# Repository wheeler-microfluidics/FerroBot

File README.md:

# FerroBot

First attempt of making a FerroBot based on https://github.com/The-Brainery/FerroBot.

This version has the option to be controlled via microcontroller or the FerroBot controller board (https://github.com/wheeler-microfluidics/FerroBot-Button-Controller.kicad)

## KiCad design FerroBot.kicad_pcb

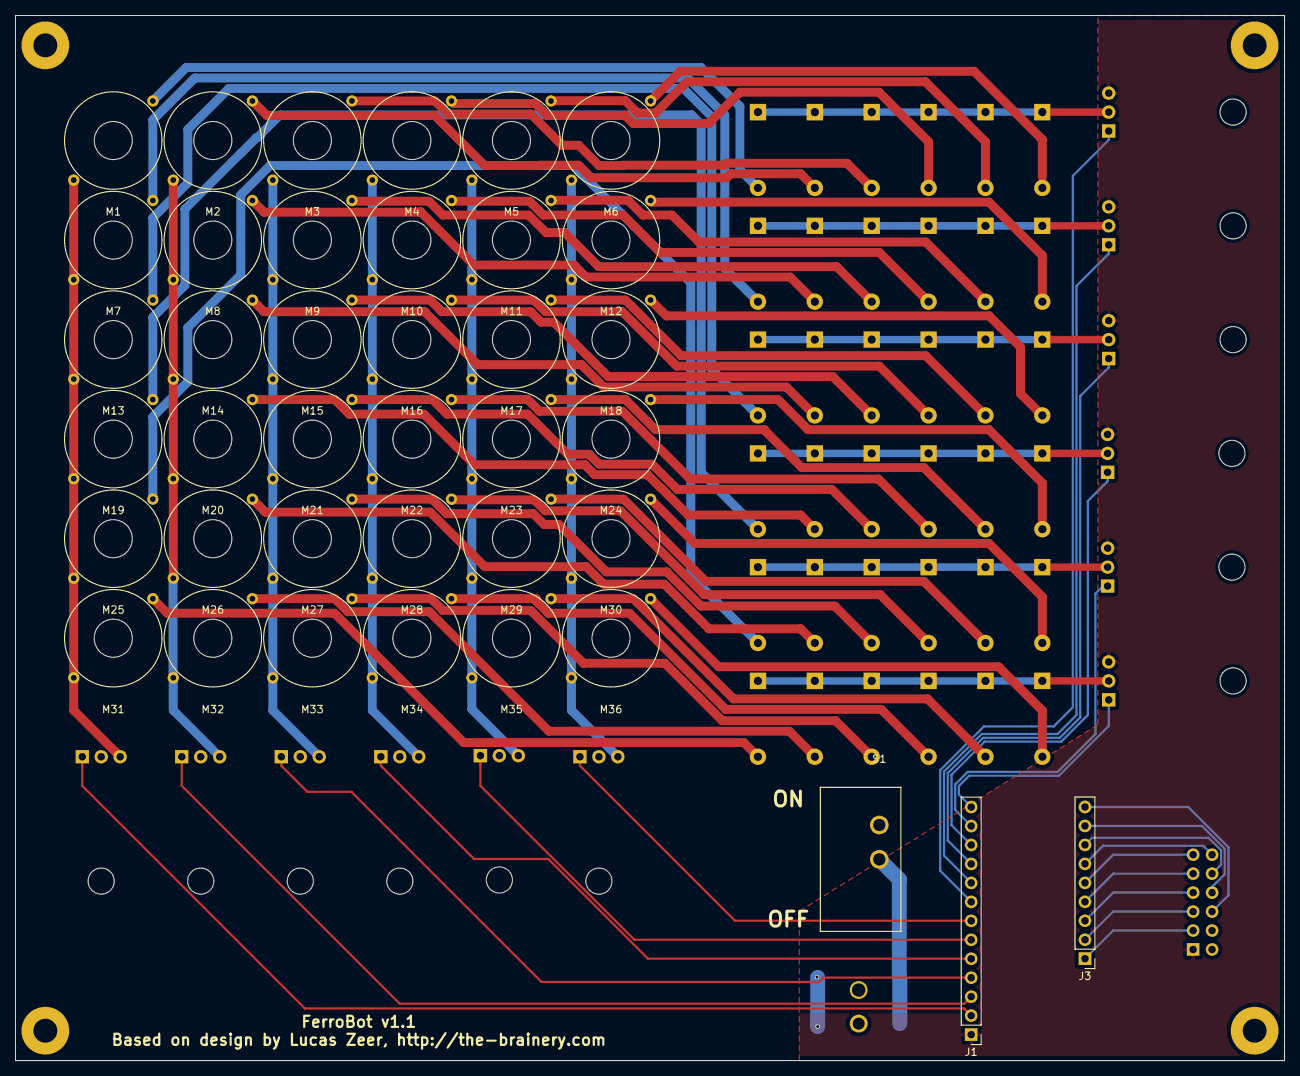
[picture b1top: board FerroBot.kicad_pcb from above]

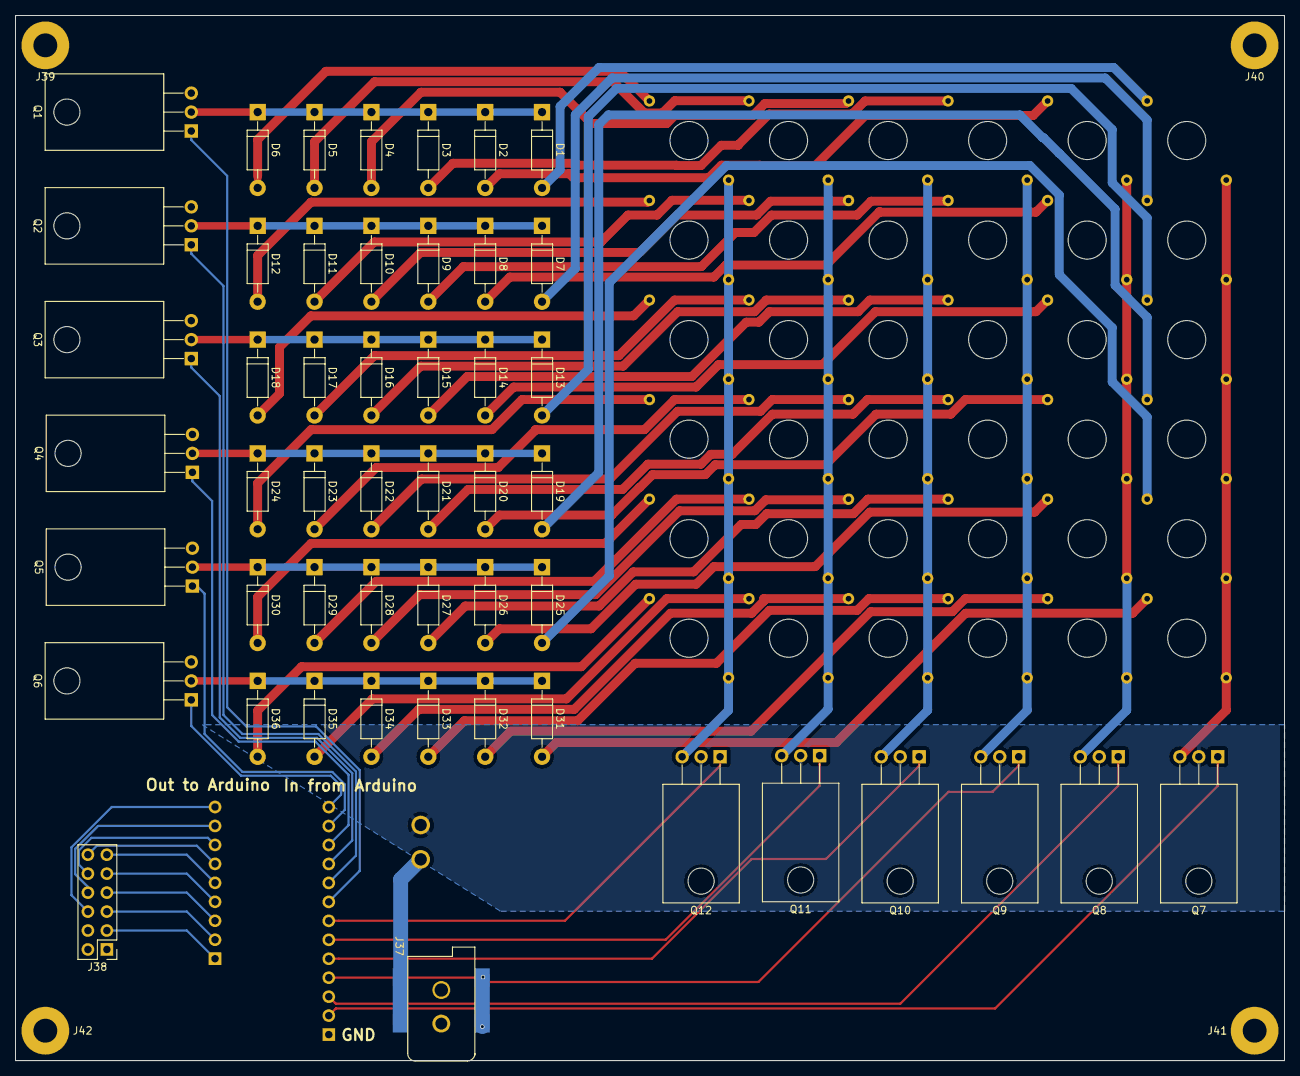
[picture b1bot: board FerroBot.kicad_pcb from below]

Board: 2 copper layers, 170.0 x 140.0 mm, 93 parts (54 on the bottom side), 72 nets.

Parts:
D1, D2, D3, D4, D5, D6, D7, D8, D9, D10, D11, D12, D13, D14, D15, D16, D17, D18, D19, D20, D21, D22, D23, D24, D25, D26, D27, D28, D29, D30, D31, D32, D33, D34, D35, D36: D_Schottky; D_DO-41_SOD81_P10.16mm_Horizontal
J1: Conn_01x13; Pin_Header_Straight_1x13_Pitch2.54mm
J3: Conn_01x09; Pin_Header_Straight_1x09_Pitch2.54mm
J37: BARREL_JACK; DC_JACK_SMD
J38: CONN_02X06; Pin_Header_Straight_2x06_Pitch2.54mm
J39, J40, J41, J42: CONN_01X01; MountingHole_3.2mm_M3_Pad
M1, M2, M3, M4, M5, M6, M7, M8, M9, M10, M11, M12, M13, M14, M15, M16, M17, M18, M19, M20, M21, M22, M23, M24, M25, M26, M27, M28, M29, M30, M31, M32, M33, M34, M35, M36: FERROBOT_MAGNET; Ferrobot_Magnet
Q1, Q2, Q3, Q4, Q5, Q6, Q7, Q8, Q9, Q10, Q11, Q12: Q_NMOS_DGS; TO-220-3_Horizontal
S1: SPST; L101_Switch

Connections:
C1CONTROL: J1.8, Q1.1
C2CONTROL: J1.9, Q2.1
C3CONTROL: J1.10, Q3.1
C4CONTROL: J1.11, Q4.1
C5CONTROL: J1.12, Q5.1
C6CONTROL: J1.13, Q6.1
COLUMN1: D1.1, D2.1, D3.1, D4.1, D5.1, D6.1, Q1.2
COLUMN2: D7.1, D8.1, D9.1, D10.1, D11.1, D12.1, Q2.2
COLUMN3: D13.1, D14.1, D15.1, D16.1, D17.1, D18.1, Q3.2
COLUMN4: D19.1, D20.1, D21.1, D22.1, D23.1, D24.1, Q4.2
COLUMN5: D25.1, D26.1, D27.1, D28.1, D29.1, D30.1, Q5.2
COLUMN6: D31.1, D32.1, D33.1, D34.1, D35.1, D36.1, Q6.2
DIODE1: D1.2, M1.2
DIODE2: D2.2, M2.2
DIODE3: D3.2, M3.2
DIODE4: D4.2, M4.2
DIODE5: D5.2, M5.2
DIODE6: D6.2, M6.2
DIODE7: D7.2, M7.2
DIODE8: D8.2, M8.2
DIODE9: D9.2, M9.2
DIODE10: D10.2, M10.2
DIODE11: D11.2, M11.2
DIODE12: D12.2, M12.2
DIODE13: D13.2, M13.2
DIODE14: D14.2, M14.2
DIODE15: D15.2, M15.2
DIODE16: D16.2, M16.2
DIODE17: D17.2, M17.2
DIODE18: D18.2, M18.2
DIODE19: D19.2, M19.2
DIODE20: D20.2, M20.2
DIODE21: D21.2, M21.2
DIODE22: D22.2, M22.2
DIODE23: D23.2, M23.2
DIODE24: D24.2, M24.2
DIODE25: D25.2, M25.2
DIODE26: D26.2, M26.2
DIODE27: D27.2, M27.2
DIODE28: D28.2, M28.2
DIODE29: D29.2, M29.2
DIODE30: D30.2, M30.2
DIODE31: D31.2, M31.2
DIODE32: D32.2, M32.2
DIODE33: D33.2, M33.2
DIODE34: D34.2, M34.2
DIODE35: D35.2, M35.2
DIODE36: D36.2, M36.2
GND: J1.1, J37.1, J37.2, J38.1, Q1.3, Q2.3, Q3.3, Q4.3, Q5.3, Q6.3
MAGNET1: J3.1, J38.3
MAGNET2: J3.2, J38.5
MAGNET3: J3.3, J38.7
MAGNET4: J3.4, J38.9
MAGNET5: J3.5, J38.11
MAGNET6: J3.6, J38.12
MAGNET7: J3.7, J38.10
MAGNET8: J3.8, J38.8
MAGNET9: J3.9, J38.6
PWR: Q7.2, Q9.2, Q10.2, Q11.2, Q12.2, S1.1
PWR_SWITCH: J37.3, S1.2
R1CONTROL: J1.2, Q7.1
R2CONTROL: J1.3, Q8.1
R3CONTROL: J1.4, Q9.1
R4CONTROL: J1.5, Q10.1
R5CONTROL: J1.6, Q11.1
R6CONTROL: J1.7, Q12.1
ROW1: M1.1, M7.1, M13.1, M19.1, M25.1, M31.1, Q7.3
ROW2: M2.1, M8.1, M14.1, M20.1, M26.1, M32.1, Q8.3
ROW3: M3.1, M9.1, M15.1, M21.1, M27.1, M33.1, Q9.3
ROW4: M4.1, M10.1, M16.1, M22.1, M28.1, M34.1, Q10.3
ROW5: M5.1, M11.1, M17.1, M23.1, M29.1, M35.1, Q11.3
ROW6: M6.1, M12.1, M18.1, M24.1, M30.1, M36.1, Q12.3

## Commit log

2018-05-18 Fix switch footprint
2018-05-24 Edit magnet footprint for better fit and shrink board
2018-06-06 Moved Teensy version to new branch, master now has generic connections to be used for any arduino
